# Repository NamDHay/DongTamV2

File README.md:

# Dự án Đồng Tâm

## Sơ đồ tổng quát

## Yêu cầu

- Điều khiển đóng cắt 16 van khí
- Đọc tín hiệu kiểm tra van có bị hư hay không
- Sử dụng thời gian thực (chưa rõ mục đích)
- Gửi thông số áp suất lúc kích van (gửi giá trị đỉnh áp suất lên server)
- Mở rộng RS485 thêm các van

## Board chính

### Các thành phần

- MOSFET kích 16 valve khí [SI2300](https://icdayroi.com/si2300ds)(SL:16)
- Diode xả ngược bảo vệ MOSFET valve khí [1N4148WS](https://www.thegioiic.com/1n4148ws-diode-chinh-luu-0-15a-75v) (SL:16)
- IC mở rộng output [74HC595](https://www.thegioiic.com/74hc595d-cn) (SL:2)
- IC mở rộng input [74HC165](https://www.thegioiic.com/74hc165d-ic-shift-register-1-element-8-bit-complementary-16-soic)(SL:2)
- Đọc tín hiệu 16 van gửi về ( 14TSSOP)
[TL084IPT](https://www.thegioiic.com/tl084ipt-ic-opamp-j-fet-amplifier-4-circuit-4mhz-14-tssop) (số lượng 4).
- Đọc áp suất cảm biến (I2C) (AMS5915 khách hàng cung cấp)
- RS485(không cách ly vì thiếu không gian) [SP3485](https://www.thegioiic.com/sp3485en-line-transceiver-8-soic)(SL:1)
- RTC  [DS3231](https://www.thegioiic.com/ds3231sn-ic-rtc-clock-calendar-16-soic) và [PCF8563](https://www.thegioiic.com/pcf8563t-ic-rtc-clock-calendar-8-soic) (PCF8563 chồng footprint với DS3231)(SL:1)
- Biến trở số (SPI) [MCP41010](http://linhkienviet.vn/mcp41010-sop8-potentiometers-10k-bien-tro-so-10k)(SL:1)
- IC nhớ lưu thông số ESP32 (I2C)(SL:1)
- Nguồn đôi 24V và 5V (Khách hàng cung cấp)
- EEPROM lưu thông số board ESP32 [24LC256](https://www.thegioiic.com/24lc256-i-sn-ic-eeprom-256kbit-8-soic) (SL:1)
- Khối chuyển từ áp sang dòng 4-20mA
- Cổng IDC 14 pin nối tới board hiển thị (SL:1)

## Board hiển thị (đã thiết kế sẵn)

- Màn hình 20x4 mở rộng bằng PCF8574 
- Còi buzzer
- Led bar
- 4 nút nhấn 

## Bảng kết nối chân

Pin Number | Function      | Device Pin | Pin Function | Device Name
----------|---------------|------------|--------------|----------------
11(PA1)   | GPIO Output   | 2 & 3      | DERE         | SP3485
12(PA2)   | UART TX 2     | 1          | RO           | 
13(PA3)   | UART RX 2     | 4          | DI           | 
15(PA5)   | GPIO Output   | 12         | Clock        | 74HC595
17(PA7)   | GPIO Output   | 14(IC1)   | Data         | 
18(PB0)   | GPIO Output   | 11         | Store        | 
33(PA12)  | GPIO Output   | 13         | OE           | 
25(PB12)  | GPIO Output   | 1          | CS           | MCP41010
26(PB13)  | SPI SCK 2     | 2          | SCK          | 
28(PB15)  | SPI MOSI 2    | 3          | MOSI         | 
30(PA9)   | UART TX 1     | 34(RXD0)   | UART RX      | ESP32
31(PA10)  | UART RX 1     | 35(TXD0)   | UART TX      | 
32(PA11)  | GPIO Ouput    | 1          | Load         | 74HC165
33(PA12)  | GPIO Output   | 15         | OE           | 
39(PB3)   | GPIO Input    | 9 (IC2)    | Data         | 
40(PB4)   | GPIO Output   | 2          | Clock        | 
42(PB6)   | I2C SCL 1     | 6 (PCF)    | I2C SCL      | "PCF8574 || DS3231"
43(PB7)   | I2C SDA 1     | 5(PCF)     | I2C SDA      | 
42(PB6)   | I2C SCL 1     | 4          | I2C SCL      | AMS5915
43(PB7)   | I2C SDA 1     | 3          | I2C SDA      |

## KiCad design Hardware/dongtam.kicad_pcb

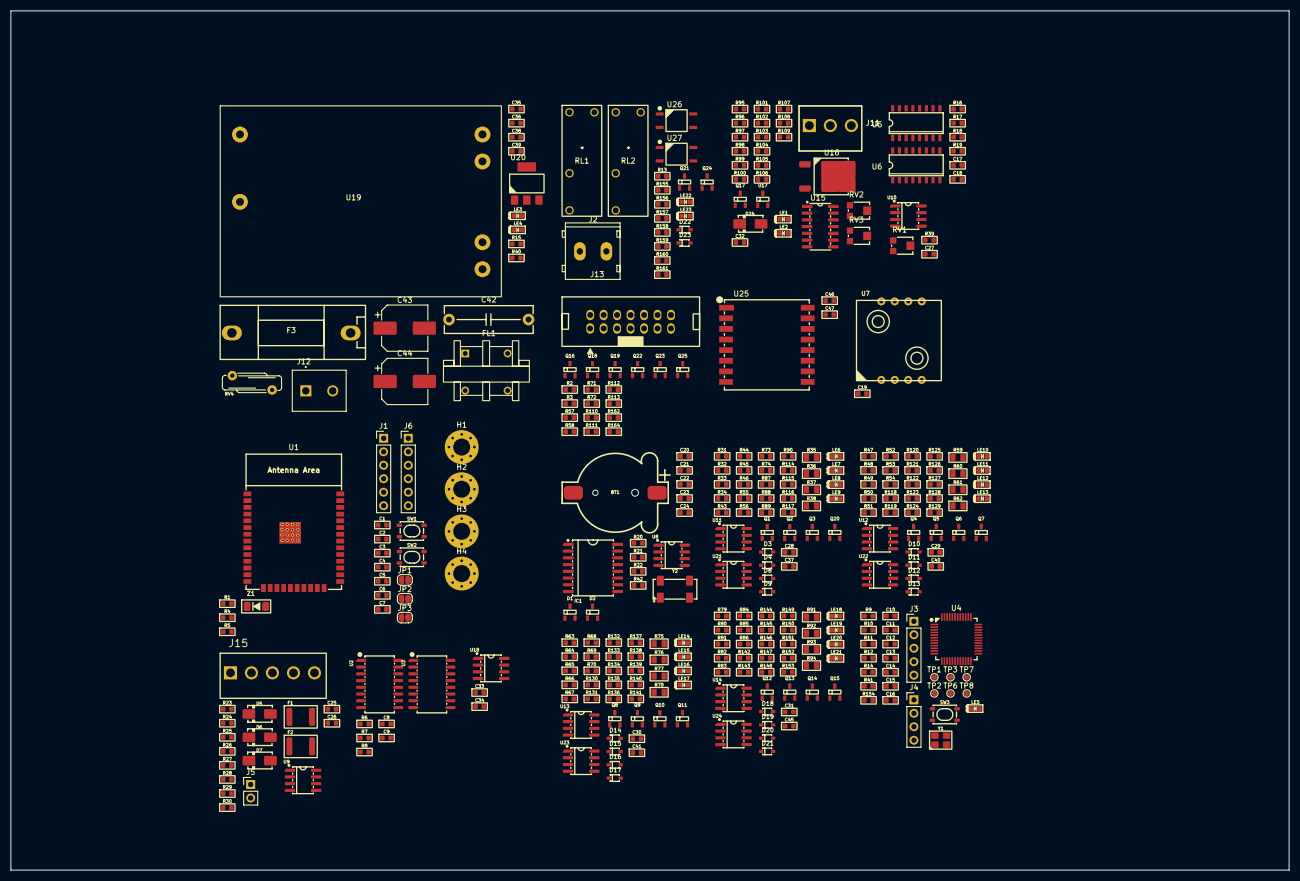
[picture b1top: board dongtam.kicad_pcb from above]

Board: 2 copper layers, 241.0 x 162.0 mm, 350 parts (0 on the bottom side), 208 nets, no tracks yet.

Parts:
BT1: CR1220; BatteryHolder_CR1220
C1, C23: 10uF; C_0603
C2, C25, C33, C35, C38, C46: 1uF; C_0603
C3, C6, C7, C8, C9, C13, C14, C15, C16, C17, C18, C19, C22, C24, C26, C27, C28, C29, C30, C31, C32, C34, C36, C37, C39, C40, C41, C45, C47: 100nF; C_0603
C4: 33pF; C_0603
C5, C20, C21: 10pF; C_0603
C10, C11: 22pF; C_0603
C12: 10nF; C_0603
C42: C; C_Rect_L16.5mm_W5.0mm_P15.00mm_MKT
C43, C44: 100uF; CP_Elec_8x10.5
D1, D2: BAT54C; SOT23-3
D3, D4, D8, D9, D10, D11, D12, D13, D14, D15, D16, D17, D18, D19, D20, D21, D22, D23: 1N4007; D_SOD323
D5, D6, D7: D_TVS; D_SMA
D24: 1N4007; D_SMA
F1, F2: Polyfuse; Fuse_1812_4532Metric
F3: Fuse; Fuse_BLX-A-P22.4mm
FL1: Filter_EMI_LL; ACFilterChokeUU9.8
H1, H2, H3, H4: MountingHole; MountingHole_3.2mm_M3_Pad_Via
IC1: RTC_DS3231M; SOIC-16W_7.5x10.3mm_P1.27mm
J1, J6: Conn_01x05_Male; PinHeader_1x06_P2.54mm_Vertical
J2: Conn_01x02_Socket; KF128-5.0-2P
J3: Conn_01x05_Male; PinHeader_1x05_P2.54mm_Vertical
J4: Conn_01x04_Male; PinHeader_1x04_P2.54mm_Vertical
J5: Conn_01x02_Male; PinHeader_1x02_P2.54mm_Vertical
J11: HT3.96mm-3P; Terminal_HT-P3.96mm-3P-Vertical-Pluggable
J12: HT-5.08mm; KF-5.08mm
J13: IDC_02x07; DC3_14PIN_2.54mm
J15: Conn_01x05_Pin; Terminal_HT-3.96mm-5P-Vertical-Pluggable
JP1, JP2, JP3: SolderJumper-2_P1.3mm_Open_RoundedPad1.0x1.5mm
LE1, LE2, LE3, LE4, LE5, LE6, LE7, LE8, LE9, LE10, LE11, LE12, LE13, LE14, LE15, LE16, LE17, LE18, LE19, LE20, LE21, LE22, LE23: Led; LED_0603
Q1, Q2, Q3, Q4, Q5, Q6, Q7, Q8, Q9, Q10, Q11, Q12, Q13, Q14, Q15, Q16, Q18, Q19, Q20, Q21, Q22, Q23, Q24, Q25: N_Mosfet; SOT23-3
Q17: NPN; SOT23-3
R1: 100; R_0603
R2, R3, R6, R7, R8, R10, R11, R16, R17, R18, R19, R57, R58, R71, R72, R110, R111, R112, R113, R162, R164: 4k7; R_0603
R4, R5, R9, R15, R25, R26, R44, R46, R73, R87, R97, R118, R120, R122, R124, R130, R132, R134, R136, R142, R144, R146, R148: 10k; R_0603
R12: 2k2; R_0603
R13, R39, R40, R42, R43, R45, R47, R48, R49, R50, R55, R56, R63, R64, R65, R66, R74, R79, R80, R81, R82, R88, R89, R90, R96, R114, R115, R116, R117, R119, R121, R123, R125, R126, R127, R128, R129, R131, R133, R135, R137, R138, R139, R140, R141, R143, R145, R147, R149, R150, R151, R152, R153, R157: 1k; R_0603
R14, R154: 10K; R_0603
R20, R22: NC; R_0603
R21: 0R; R_0603
R23, R24, R27, R28, R29: 120R; R_0603
R30, R31, R32, R33, R34, R41, R51, R52, R53, R54, R67, R68, R69, R70, R83, R84, R85, R86, R155, R156: 1M; R_0603
R35, R36, R37, R38, R59, R60, R61, R62, R75, R76, R77, R78, R91, R92, R93, R94: 0R5; R_0805
R95: 220R; R_0603
R98: 560R; R_0603
R99, R100: 100k; R_0603
R101, R102, R103, R104, R105, R106, R109: 820k; R_0603
R107: 100R; R_0603
R108: 680k; R_0603
R158, R161: 5k; R_0603
R159, R160: R; R_0603
RL1, RL2: Relay_G5NB-1A-E_DC5; Relay_G5NB-1A-E DC5
RV1: TC33X_10k; Potentiometer_Bourns_TC33X_Vertical
RV2, RV3: 100k; Potentiometer_Bourns_TC33X_Vertical
RV4: Varistor; RV_Disc_D12mm_W5.8mm_P7.5mm
SW1, SW2, SW3: SW_Push; SW_SPST_PTS810
TP1, TP2, TP3, TP6, TP7, TP8: TestPoint; TestPoint_Pad_D1.0mm
U1: ESP32-WROOM-32UE; ESP32-WROOM-32E
U2, U3: 74HC165; SOIC-16W_5.3x10.2mm_P1.27mm
U4: STM32F103C8Tx; LQFP-48_7x7mm_P0.5mm
U5, U6: 74HC595; SOIC-16W_3.92x10.2mm
U7: AMS5915
U8: PCF8563TS; SOIC-8_3.9x4.9mm_P1.27mm
U9: SP3485EN; SOIC-8_3.9x4.9mm_P1.27mm
U10: MCP41010; SOIC-8_3.9x4.9mm_P1.27mm
U11, U12, U13, U14, U21, U22, U23, U24: LM393; SOIC-8_3.9x4.9mm_P1.27mm
U15: LM324; SOIC14
U16: LM317_TO-252; TO-252-2
U17: TL431; SOT23-3
U18: 24LC256; SOIC-8_3.9x4.9mm_P1.27mm
U19: AM22-24W2405V; DualPowerSupply_AM22-24W2405V
U20: LD1117; SOT233
U25: Ai-Thinker-Ra-02; MODULE_RA-02_LORA
U26, U27: Opto; OPTO_EL357N-G
Y1: 8MHz; Crystal_3225_4P_3.2x2.6mm
Y2: 32.768kHz; Crystal_MC306
Z1: D_Zener; D_MiniMELF

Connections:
+3V3: C8.2, C9.2, C13.1, C14.1, C15.1, C16.1, C19.2, C23.2, C24.2, C25.2, C27.1, C28.1, C29.1, C30.1, C31.1, C33.1, C34.1, C37.1, C38.2, C39.2, C40.1, C41.1, C45.1, C46.1, C47.1, D2.1, IC1.2 (VCC), J1.6, J3.4, J4.3, J6.6, J13.13, JP1.1 (A), LE5.1, Q16.1 (G), Q18.1 (G), Q19.1 (G), Q22.1 (G), Q23.1 (G), Q25.1 (G), R3.1, R4.1, R5.1, R6.1, R7.1, R8.1, R9.1, R10.1, R11.1, R26.1, R42.1, R44.1, R45.2, R46.1, R56.2, R57.1, R58.1, R73.1, R87.1, R89.2, R90.2, R110.1, R111.1, R118.1, R120.1, R122.1, R124.1, R126.2, R127.2, R128.2, R129.2, R130.1, R132.1, R134.1, R136.1, R138.2, R139.2, R140.2, R141.2, R142.1, R144.1, R146.1, R148.1, R150.2, R151.2, R152.2, R153.2, R159.2, R160.2, R162.1, RV1.3, U2.16 (VCC), U3.16 (VCC), U4.9 (VDDA), U4.24 (VDD), U4.36 (VDD), U4.48 (VDD), U7.2 (VCC), U9.8 (VCC), U10.5 (PA0), U10.8 (VDD), U11.8 (V+), U12.8 (V+), U13.8 (V+), U14.8 (V+), U18.8 (VCC), U20.2 (VO), U21.8 (V+), U22.8 (V+), U23.8 (V+), U24.8 (V+), U25.3 (VDD)
+5V: C17.2, C18.2, C35.2, C36.2, C44.1, D22.2, D23.2, J3.5, J13.2, R2.1, R16.1, R17.1, R18.1, R19.1, R22.1, R40.1, R71.1, R72.1, R112.1, R113.1, R157.1, R164.1, RL2.1, U5.10 (~SRCLR), U5.16 (VCC), U6.10 (~SRCLR), U6.16 (VCC), U19.6 (+5V), U20.3 (VI)
+24V: C43.1, D3.2, D4.2, D8.2, D9.2, D10.2, D11.2, D12.2, D13.2, D14.2, D15.2, D16.2, D17.2, D18.2, D19.2, D20.2, D21.2, R15.1, U19.3 (+24V)
/4-20mAConverter/DAC_4_20mA: R99.1, U1.10 (IO25), U15.3 (+)
/4-20mAConverter/LM137_IN: C32.1, D24.2, Q17.3 (C), U15.4 (V+), U16.3 (VI)
/4-20mAConverter/LM137_OUT: R95.1, R97.1, R98.2, U16.2 (VO)
/4-20mAConverter/TransB: Q17.1 (B), U15.8
/16_VALVE_CONTROL/595.RCLK: R19.2, U4.18 (PB0), U5.12 (RCLK), U6.12 (RCLK)
/16_VALVE_CONTROL/595.SER: R18.2, U4.17 (PA7), U5.14 (SER)
/16_VALVE_CONTROL/595.SRCLK: R17.2, U4.15 (PA5), U5.11 (SRCLK), U6.11 (SRCLK)
/16_VALVE_CONTROL/OE: R16.2, U2.15 (~CE), U3.15 (~CE), U4.33 (PA12), U5.13 (~OE), U6.13 (~OE)
/16_VALVE_CONTROL/VI_1: Q20.1 (G), R31.1, R114.1, U5.15 (QA)
/16_VALVE_CONTROL/VI_2: Q1.1 (G), R32.1, R115.1, U5.1 (QB)
/16_VALVE_CONTROL/VI_3: Q2.1 (G), R33.1, R116.1, U5.2 (QC)
/16_VALVE_CONTROL/VI_4: Q3.1 (G), R34.1, R117.1, U5.3 (QD)
/16_VALVE_CONTROL/VI_5: Q4.1 (G), R47.1, R51.1, U5.4 (QE)
/16_VALVE_CONTROL/VI_6: Q5.1 (G), R49.1, R52.1, U5.5 (QF)
/16_VALVE_CONTROL/VI_7: Q6.1 (G), R48.1, R53.1, U5.6 (QG)
/16_VALVE_CONTROL/VI_8: Q7.1 (G), R50.1, R54.1, U5.7 (QH)
/16_VALVE_CONTROL/VI_9: Q8.1 (G), R63.1, R67.1, U6.15 (QA)
/16_VALVE_CONTROL/VI_10: Q9.1 (G), R65.1, R68.1, U6.1 (QB)
/16_VALVE_CONTROL/VI_11: Q10.1 (G), R64.1, R69.1, U6.2 (QC)
/16_VALVE_CONTROL/VI_12: Q11.1 (G), R66.1, R70.1, U6.3 (QD)
/16_VALVE_CONTROL/VI_13: Q12.1 (G), R79.1, R83.1, U6.4 (QE)
/16_VALVE_CONTROL/VI_14: Q13.1 (G), R81.1, R84.1, U6.5 (QF)
/16_VALVE_CONTROL/VI_15: Q14.1 (G), R80.1, R85.1, U6.6 (QG)
/16_VALVE_CONTROL/VI_16: Q15.1 (G), R82.1, R86.1, U6.7 (QH)
/EEPROM/24256.SCL: Q19.2 (S), R111.2, U1.36 (IO22), U18.6 (SCL)
/EEPROM/24256.SDA: Q18.2 (S), R110.2, U1.33 (IO21), U18.5 (SDA)
/ESP32/BOOT: C6.1, J1.5, R4.2, SW1.1, U1.25 (IO0)
/ESP32/BT.s1: J13.11, U1.7 (IO35)
/ESP32/BT.s2: J13.9, U1.6 (IO34)
/ESP32/BT.s3: J13.7, U1.5 (SENSOR_VN)
/ESP32/BT.s4: J13.5, U1.4 (SENSOR_VP)
/ESP32/ESP_74595.RCLK: Q22.2 (S), R57.2, U1.29 (IO5)
/ESP32/ESP_74595.SER: Q16.2 (S), R3.2, U1.37 (IO23)
/ESP32/ESP_74595.SRCLK: Q23.2 (S), R58.2, U1.30 (IO18)
/ESP32/RST: C7.1, J1.2, R5.2, SW2.2, U1.3 (EN)
/ESP32/RX: J1.4, U1.34 (RXD0/IO3)
/ESP32/RX_ESP32: JP2.2 (B), U4.30 (PA9)
/ESP32/TCK: J6.4, U1.16 (IO13)
/ESP32/TDI: J6.2, U1.14 (IO12)
/ESP32/TDO: J6.3, U1.23 (IO15)
/ESP32/TMS: J6.5, U1.13 (IO14)
/ESP32/TX: J1.3, U1.35 (TXD0/IO1)
/ESP32/TX_ESP32: JP3.2 (B), U4.31 (PA10)
/ESP32/VDD_ESP32: C1.1, C2.1, C3.1, C4.1, C5.1, JP1.2 (B), U1.2 (VDD), Z1.2
/GET_16_VALVE_STAGE/74HC165.DATA: R6.2, U2.9 (Q7), U4.39 (PB3)
/GET_16_VALVE_STAGE/74HC165.LOAD: R8.2, U2.1 (~PL), U3.1 (~PL), U4.32 (PA11)
/GET_16_VALVE_STAGE/74HC165.SCK: R7.2, U2.2 (CP), U3.2 (CP), U4.40 (PB4)
/GET_16_VALVE_STAGE/MCP41010.CS: U4.25 (PB12), U10.1 (~CS)
/GET_16_VALVE_STAGE/MCP41010.MOSI: U4.28 (PB15), U10.3 (SI), U25.14 (MOSI)
/GET_16_VALVE_STAGE/MCP41010.SCK: U4.26 (PB13), U10.2 (SCK), U25.12 (SCK)
/GET_16_VALVE_STAGE/OPAMP/1_TL084IPT/VAN1-: D8.1, Q20.3 (D)
/GET_16_VALVE_STAGE/OPAMP/1_TL084IPT/VAN2-: D9.1, Q1.3 (D)
/GET_16_VALVE_STAGE/OPAMP/1_TL084IPT/VAN3-: D3.1, Q2.3 (D)
/GET_16_VALVE_STAGE/OPAMP/1_TL084IPT/VAN4-: D4.1, Q3.3 (D)
/GET_16_VALVE_STAGE/OPAMP/2_TL084IPT/VAN1-: D10.1, Q4.3 (D)
/GET_16_VALVE_STAGE/OPAMP/2_TL084IPT/VAN2-: D11.1, Q5.3 (D)
/GET_16_VALVE_STAGE/OPAMP/2_TL084IPT/VAN3-: D12.1, Q6.3 (D)
/GET_16_VALVE_STAGE/OPAMP/2_TL084IPT/VAN4-: D13.1, Q7.3 (D)
/GET_16_VALVE_STAGE/OPAMP/3_TL084IPT/VAN1-: D14.1, Q8.3 (D)
/GET_16_VALVE_STAGE/OPAMP/3_TL084IPT/VAN2-: D15.1, Q9.3 (D)
/GET_16_VALVE_STAGE/OPAMP/3_TL084IPT/VAN3-: D16.1, Q10.3 (D)
/GET_16_VALVE_STAGE/OPAMP/3_TL084IPT/VAN4-: D17.1, Q11.3 (D)
/GET_16_VALVE_STAGE/OPAMP/4_TL084IPT/VAN1-: D18.1, Q12.3 (D)
/GET_16_VALVE_STAGE/OPAMP/4_TL084IPT/VAN2-: D19.1, Q13.3 (D)
/GET_16_VALVE_STAGE/OPAMP/4_TL084IPT/VAN3-: D20.1, Q14.3 (D)
/GET_16_VALVE_STAGE/OPAMP/4_TL084IPT/VAN4-: D21.1, Q15.3 (D)
/GET_16_VALVE_STAGE/OPAMP/PW0_MCP41010: R39.1, R43.1, R44.2, R46.2, R55.1, R73.2, R74.1, R87.2, R88.1, R118.2, R119.1, R120.2, R121.1, R122.2, R123.1, R124.2, R125.1, R130.2, R131.1, R132.2, R133.1, R134.2, R135.1, R136.2, R137.1, R142.2, R143.1, R144.2, R145.1, R146.2, R147.1, R148.2, R149.1, RV1.2, U10.6 (PW0), U11.2 (-), U11.6 (-), U12.2 (-), U12.6 (-), U13.2 (-), U13.6 (-), U14.2 (-), U14.6 (-), U21.2 (-), U21.6 (-), U22.2 (-), U22.6 (-), U23.2 (-), U23.6 (-), U24.2 (-), U24.6 (-)
/GET_16_VALVE_STAGE/OPAMP/VO_1: R56.1, U2.11 (D0), U11.1
/GET_16_VALVE_STAGE/OPAMP/VO_2: R45.1, U2.12 (D1), U11.7
/GET_16_VALVE_STAGE/OPAMP/VO_3: R89.1, U2.13 (D2), U21.1
/GET_16_VALVE_STAGE/OPAMP/VO_4: R90.1, U2.14 (D3), U21.7
/GET_16_VALVE_STAGE/OPAMP/VO_5: R126.1, U2.3 (D4), U12.1
/GET_16_VALVE_STAGE/OPAMP/VO_6: R128.1, U2.4 (D5), U12.7
/GET_16_VALVE_STAGE/OPAMP/VO_7: R127.1, U2.5 (D6), U22.1
/GET_16_VALVE_STAGE/OPAMP/VO_8: R129.1, U2.6 (D7), U22.7
/GET_16_VALVE_STAGE/OPAMP/VO_9: R138.1, U3.11 (D0), U13.1
/GET_16_VALVE_STAGE/OPAMP/VO_10: R140.1, U3.12 (D1), U13.7
/GET_16_VALVE_STAGE/OPAMP/VO_11: R139.1, U3.13 (D2), U23.1
/GET_16_VALVE_STAGE/OPAMP/VO_12: R141.1, U3.14 (D3), U23.7
/GET_16_VALVE_STAGE/OPAMP/VO_13: R150.1, U3.3 (D4), U14.1
/GET_16_VALVE_STAGE/OPAMP/VO_14: R152.1, U3.4 (D5), U14.7
/GET_16_VALVE_STAGE/OPAMP/VO_15: R151.1, U3.5 (D6), U24.1
/GET_16_VALVE_STAGE/OPAMP/VO_16: R153.1, U3.6 (D7), U24.7
/IDC14pin/74595OE: Q25.2 (S), R162.2
/IDC14pin/74595_OE: J13.8, Q25.3 (D), R164.2
/IDC14pin/IC74595_RCLK: J13.10, Q22.3 (D), R71.2
/IDC14pin/IC74595_SER: J13.6, Q16.3 (D), R2.2
/IDC14pin/IC74595_SRCLK: J13.12, Q23.3 (D), R72.2
/IDC14pin/LCD_I2C_LOGIC_SCL: J13.3, Q19.3 (D), R113.2
/IDC14pin/LCD_I2C_LOGIDC_SDA: J13.4, Q18.3 (D), R112.2
/LORA/LORA_CS: U4.27 (PB14), U25.15 (~NSS)
/LORA/LORA_INT: U4.38 (PA15), U25.5 (DIO0)
/LORA/LORA_RST: U4.10 (PA0), U25.4 (~RESET)
/PRESSURE_SENSOR/i2c.SCL: IC1.16 (SCL), R10.2, U4.42 (PB6), U7.4 (SCL), U8.6 (SCL)
/PRESSURE_SENSOR/i2c.SDA: IC1.15 (SDA), R11.2, U4.43 (PB7), U7.3 (SDA), U8.5 (SDA)
/RELAY_OPTO/OPTO1: J2.1, R158.2, R159.1, U26.4
/RELAY_OPTO/OPTO2: J2.2, R160.1, R161.2, U27.4
/RELAY_OPTO/RL1: Q21.1 (G), R155.1
/RELAY_OPTO/RL2: Q24.1 (G), R156.1
/RS485/A1_RS485: D5.2, D6.1, F1.1, R27.2, R29.1
/RS485/A2_RS485: R26.2, R27.1, U9.6 (A)
/RS485/A_RS485: F1.2, J15.4, J15.5
/RS485/B1_RS485: D6.2, D7.1, F2.1, J5.1, R28.2
/RS485/B2_RS485: R25.1, R28.1, U9.7 (B)
/RS485/B_RS485: F2.2, J15.2, J15.3
/RS485/RS485.DERE: U4.11 (PA1), U9.2 (~RE), U9.3 (DE)
/RS485/RS485.RX: R24.1, U4.12 (PA2)
/RS485/RS485.TX: R23.1, U4.13 (PA3)
/RTC/Vbat: BT1.1 (+), D1.2, D2.3, R20.2, R21.1
/STM32F103C8T6/LED: R12.1, U4.19 (PB1)
/STM32F103C8T6/PD0: C10.2, R41.1, U4.5 (PD0), Y1.1
/STM32F103C8T6/PD1: C11.1, R41.2, U4.6 (PD1), Y1.3
/STM32F103C8T6/RST: C12.2, R9.2, SW3.1, U4.7 (NRST)
/STM32F103C8T6/RX_LOG: J4.2, U4.22 (PB11)
/STM32F103C8T6/SWCLK: J3.1, U4.37 (PA14)
/STM32F103C8T6/SWDIO: J3.2, U4.34 (PA13)
/STM32F103C8T6/TX_LOG: J4.1, U4.21 (PB10)
Earth: C26.1, J15.1, R30.1
GND: BT1.2 (-), C1.2, C2.2, C3.2, C4.2, C5.2, C6.2, C7.2, C8.1, C9.1, C10.1, C11.2, C12.1, C13.2, C14.2, C15.2, C16.2, C17.1, C18.1, C19.1, C20.2, C21.2, C22.2, C23.1, C24.1, C25.1, C26.2, C27.2, C28.2, C29.2, C30.2, C31.2, C32.2, C33.2, C34.2, C35.1, C36.1, C37.2, C38.1, C39.1, C40.2, C41.2, C43.2, C44.2, C45.2, C46.2, C47.2, D5.1, D7.2, IC1.5 (GND), IC1.6 (GND), IC1.7 (GND), IC1.8 (GND), IC1.9 (GND), IC1.10 (GND), IC1.11 (GND), IC1.12 (GND), IC1.13 (GND), J1.1, J3.3, J4.4, J6.1, J11.1, J13.1, J13.14, LE1.2, LE3.2, LE4.2, LE6.2, LE7.2, LE8.2, LE9.2, LE10.2, LE11.2, LE12.2, LE13.2, LE14.2, LE15.2, LE16.2, LE17.2, LE18.2, LE19.2, LE20.2, LE21.2, Q21.2 (S), Q24.2 (S), R14.1, R25.2, R30.2, R31.2, R32.2, R33.2, R34.2, R35.2, R36.2, R37.2, R38.2, R39.2, R43.2, R51.2, R52.2, R53.2, R54.2, R55.2, R59.2, R60.2, R61.2, R62.2, R67.2, R68.2, R69.2, R70.2, R74.2, R75.2, R76.2, R77.2, R78.2, R83.2, R84.2, R85.2, R86.2, R88.2, R91.2, R92.2, R93.2, R94.2, R96.2, R99.2, R103.2, R104.2, R119.2, R121.2, R123.2, R125.2, R131.2, R133.2, R135.2, R137.2, R143.2, R145.2, R147.2, R149.2, R154.1, R155.2, R156.2, RV1.1, RV2.3, RV3.3, SW1.2, SW2.1, SW3.2, U1.1 (GND), U1.15 (GND), U1.38 (GND), U1.39 (GND), U2.8 (GND), U3.8 (GND), U4.8 (VSSA), U4.23 (VSS), U4.35 (VSS), U4.47 (VSS), U5.8 (GND), U6.8 (GND), U7.1 (GND), U8.4 (VSS), U9.5 (GND), U10.4 (VSS), U10.7 (PB0), U11.4 (V-), U12.4 (V-), U13.4 (V-), U14.4 (V-), U15.11 (V-), U17.3 (A), U18.1 (A0), U18.2 (A1), U18.3 (A2), U18.4 (GND), U18.7 (WP), U19.4 (GND), U19.5 (GND), U20.1 (GND), U21.4 (V-), U22.4 (V-), U23.4 (V-), U24.4 (V-), U25.1 (GND), U25.2 (GND), U25.9 (GND), U25.16 (GND), U26.2, U26.3, U27.2, U27.3, Y1.2, Y1.4, Y2.2, Y2.3, Z1.1
unnamed: C42.2, F3.2, FL1.3, RV4.2
unnamed: D1.1, R42.2
unnamed: D1.3, IC1.14 (VBAT)
unnamed: J5.2, R29.2
unnamed: J11.2, LE2.2
unnamed: F3.1, J12.1
unnamed: C42.1, FL1.1, J12.2, RV4.1
unnamed: JP2.1 (A), R1.2
unnamed: JP3.1 (A), U1.28 (IO17)
unnamed: LE1.1, R97.2
unnamed: LE2.1, R107.1, R109.2
unnamed: LE3.1, R15.2
unnamed: LE4.1, R40.2
unnamed: LE5.2, R12.2
unnamed: LE6.1, R114.2
unnamed: LE7.1, R115.2
unnamed: LE8.1, R116.2
unnamed: LE9.1, R117.2
unnamed: LE10.1, R47.2
unnamed: LE11.1, R48.2
unnamed: LE12.1, R49.2
unnamed: LE13.1, R50.2
unnamed: LE14.1, R63.2
unnamed: LE15.1, R64.2
unnamed: LE16.1, R65.2
unnamed: LE17.1, R66.2
unnamed: LE18.1, R79.2
unnamed: LE19.1, R80.2
unnamed: LE20.1, R81.2
unnamed: LE21.1, R82.2
unnamed: LE22.1, R13.2
unnamed: LE23.1, R157.2
unnamed: Q1.2 (S), R36.1, U11.5 (+)
unnamed: Q2.2 (S), R37.1, U21.3 (+)
unnamed: Q3.2 (S), R38.1, U21.5 (+)
unnamed: Q4.2 (S), R59.1, U12.3 (+)
unnamed: Q5.2 (S), R60.1, U12.5 (+)
unnamed: Q6.2 (S), R61.1, U22.3 (+)
unnamed: Q7.2 (S), R62.1, U22.5 (+)
unnamed: Q8.2 (S), R75.1, U13.3 (+)
unnamed: Q9.2 (S), R76.1, U13.5 (+)
unnamed: Q10.2 (S), R77.1, U23.3 (+)
unnamed: Q11.2 (S), R78.1, U23.5 (+)
unnamed: Q12.2 (S), R91.1, U14.3 (+)
unnamed: Q13.2 (S), R92.1, U14.5 (+)
unnamed: Q14.2 (S), R93.1, U24.3 (+)
unnamed: Q15.2 (S), R94.1, U24.5 (+)
unnamed: Q17.2 (E), R105.2, R107.2
unnamed: Q20.2 (S), R35.1, U11.3 (+)
unnamed: D22.1, LE22.2, Q21.3 (D), RL1.4
unnamed: D23.1, LE23.2, Q24.3 (D), RL2.4
unnamed: R13.1, RL1.1
unnamed: R100.1, RV2.1
unnamed: R101.1, RV3.2
unnamed: R106.2, R108.1, U15.7
unnamed: R158.1, U26.1
unnamed: R161.1, U27.1
unnamed: R1.1, U1.27 (IO16)
unnamed: U2.10 (DS), U3.9 (Q7)
unnamed: R14.2, U4.44 (BOOT0)
unnamed: TP8.1, U4.14 (PA4)
unnamed: TP7.1, U4.16 (PA6)
unnamed: TP6.1, U4.29 (PA8)
unnamed: R154.2, U4.20 (PB2)
unnamed: TP1.1, U4.41 (PB5)
unnamed: TP2.1, U4.45 (PB8)
unnamed: TP3.1, U4.46 (PB9)
unnamed: U5.9 (QH'), U6.14 (SER)
unnamed: C20.1, U8.1 (OSCI), Y2.1
unnamed: C21.1, U8.2 (OSCO), Y2.4
unnamed: C22.1, R21.2, R22.2, U8.8 (VDD)
unnamed: R20.1, U8.3 (~INT)
unnamed: R23.2, U9.4 (DI)
unnamed: R24.2, U9.1 (RO)
unnamed: RV3.1, U15.1, U15.2 (-)
unnamed: R101.2, R102.1, U15.5 (+)
unnamed: R103.1, R106.1, U15.6 (-)
unnamed: R108.2, R109.1, U15.10 (+)
unnamed: R104.1, R105.1, U15.9 (-)
unnamed: RV2.2, U15.12 (+)
unnamed: R102.2, U15.13 (-), U15.14
unnamed: R95.2, R96.1, U16.1 (ADJ)
unnamed: R98.1, R100.2, U17.1 (K), U17.2 (REF)
unnamed: FL1.2, U19.1 (L)
unnamed: FL1.4, U19.2 (N)
VCC: D24.1, J11.3

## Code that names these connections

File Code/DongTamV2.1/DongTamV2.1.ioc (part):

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Mcu.Name=STM32F103C(8-B)Tx
Mcu.Package=LQFP48
Mcu.UserName=STM32F103CBTx
PA10.Mode=Asynchronous
PA10.Signal=USART1_RX
PA11.GPIOParameters=GPIO_Label
PA11.GPIO_Label=_74HC165_LOAD
PA11.Signal=GPIO_Output
PA12.GPIOParameters=GPIO_Label
PA12.GPIO_Label=OE
PA12.Signal=GPIO_Output
PA13.Mode=Serial_Wire
PA13.Signal=SYS_JTMS-SWDIO
PA14.Mode=Serial_Wire
PA14.Signal=SYS_JTCK-SWCLK
PA5.GPIOParameters=GPIO_Label
PA5.GPIO_Label=_74HC595_CLK
PA5.Signal=GPIO_Output
PA7.GPIOParameters=GPIO_Label
PA7.GPIO_Label=_74HC595_DATA
PA7.Signal=GPIO_Output
PA9.Mode=Asynchronous
PA9.Signal=USART1_TX
PB0.GPIOParameters=GPIO_Label
PB0.GPIO_Label=_74HC595_STORE
PB0.Signal=GPIO_Output
PB1.GPIOParameters=GPIO_Label
PB1.GPIO_Label=UserLED
PB1.Signal=GPIO_Output
PB10.Mode=Asynchronous
PB10.Signal=USART3_TX
PB11.Mode=Asynchronous
PB11.Signal=USART3_RX
PB3.GPIOParameters=GPIO_Label
PB3.GPIO_Label=_74HC165_DATA
PB3.Signal=GPIO_Input
PB4.GPIOParameters=GPIO_Label
PB4.GPIO_Label=_74HC165_CLK
PB4.Signal=GPIO_Output
PB6.Mode=I2C
PB6.Signal=I2C1_SCL
PB7.Mode=I2C
PB7.Signal=I2C1_SDA
PD0-OSC_IN.Mode=HSE-External-Oscillator
PD0-OSC_IN.Signal=RCC_OSC_IN
PD1-OSC_OUT.Mode=HSE-External-Oscillator
PD1-OSC_OUT.Signal=RCC_OSC_OUT
board=custom

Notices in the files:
parts and their libraries:
Copyright 2021 Accelerated Designs. All rights reserved.
